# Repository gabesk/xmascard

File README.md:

# xmascard
Merry Christmas!

Of course, this is a little late for Christmas; by now it's probably closer in temperature in the southern hemisphere. Nevertheless, better late than never.

Welcome to the Electronic Christmas Tree Christmas Card. As you no doubt figured out already, to get started just flip the switch and enjoy the light show. (If it’s not working, try moving the battery around a little; the bottom doesn’t always make a solid connection to the board.)

Additionally, this board is intended to be at least somewhat more than just an amusement; you can do things with it, and the entire schematic and program are open source on GitHub for you to see.

It’s powered by a Xilinx FPGA, and you can add new patterns by connecting a serial cable to three pins near the FPGA with the included USB-serial adapter.

## History
The idea of this board started when Emily was playing with an Arduino one Christmas while I was looking at one of the myriad cards we’d received from friends, and I was remarking that it would be neat to take one of our Arduinos, some leftover LEDs, and see what sort of Christmas tree shaped thing we could make as a geeky card of some sort. The Arduino had 13 I/O ports, so a few minutes of brainstorming later, she came up with a 12 LED Christmas tree that looked neat.

As is my style, I couldn't leave well enough alone and keep things simple, however. First, as an undergrad I'd designed my own printed circuit boards (PCBs) and thought this would be a good excuse to re-learn how to do it. So, instead of a few LEDs wired up to an Arduino, it turned into a custom board. Additionally, I did my master’s thesis on FPGAs and I wanted an excuse both to work with them again, as well as the opportunity to introduce people to them. Given that, I thought it would be fun to use an FPGA in this Christmas card because it's typically seen as this exotic thing that is expensive and only used in specialize projects, and I wanted to change that perception.

This idea was actually conceived in January of 2015; I had no idea it would be so hard or take so long, but here we are, a year and a half later and I've finally stopped procrastinating enough to get something out the door.

## Interacting with the board
Initially, when this was just going to be a simple one-month project, the goal was just to display a pretty light pattern when you flipped the switch.

However, eventually the former-TA inside got the better of me and I decided I wanted to make it a little more interesting than just something you looked at once and put in a drawer. Toward that end, you'll also find some additional gizmos that you can use, with some assembly required, to interact with the board with your computer.

Included with the board are a USB-serial converter cable, a voltage regulator board, and some jumper wires to connect them together.

To get started, connect those pieces to the FPGA according to the following diagram:

If you're on a Windows or Linux computer, you're all set to run the programs.

If you're on a Mac, you'll need to download and install the driver for the USB-serial converter. Follow [the instructions](https://learn.adafruit.com/adafruits-raspberry-pi-lesson-5-using-a-console-cable/software-installation-mac) on AdaFruit's site this website for the SiLabs CP210X Drivers.

That done, double click the `light_control.py` file on your computer. It should open a window that looks similar to the following:

Click **Connect**, and follow the instructions. It will ask you to plug in the Christmas Tree board, and if all goes well, it will print that it was successfully connected in the bottom of the window.

Now that you're connected, click any of the lights on the tree. They should change on the board, too! :)

## Creating your own patterns
What else can you do? Well, you can make your own patterns, using the `convert_animation_file.py` and `upload_new_pattern.py` programs.

These programs accept text files containing animations patterns and downloads them to the board for display.

The animation files work like so:

Each step in the animation is specified on a line. Each line specifies the brightness of the LEDs, from the top left to the bottom right. Each LED is two digits from 0 to 7 for the red, then green brightness. The value 0 is off, while 7 is all the way bright. For readability, spaces can be added as desired and are ignored.

For example, to light the red LED on the top, then the entire row of green on the bottom, the line would look like the following:

```
70  00  00 00  00 00 00  07 07 07 07  00
```

Since that can still be hard to read, you can alternately put the LEDs on different lines and separate each step in the animation with a blank line.

This allows you to write the pattern out visually. For example, the above example could also be written as:

```
            70
            00
          00  00
        00  00  00
      07  07  07  07
            00
```

The animation runs at a fixed speed of # frames per second, and the board stores 256 animation steps for a total of # seconds of animation. If you don't use all 256 frames of animation, the program will just repeat the last frame until memory is full.

In order to make it a little easier to create animations, you can tell the program to fade between animation steps automatically.
For example, to create an animation which fades between all the LEDs on, off again, then back on, create a text file like so:

```
set_marker
       77
       77
     77  77
   77  77  77
 77  77  77  77
       77
       77
fade_to
       00
       00
     00  00
   00  00  00
 00  00  00  00
       00
fade_to
       77
       77
     77  77
   77  77  77
 77  77  77  77
       77
       77
repeat_forever
```

Suppose your text file is named animation.txt. First, convert it to an FPGA memory entry like so:
```
convert_animation_file.py animation.txt memory.txt
```
Next, program it to the FPGA like so:
```
upload_new_pattern.py COM3 memory.txt
```
You can find the correct value to use for COM3 by running the `light_control.py` and looking at the value in the box at the bottom of the program after clicking **Connect**.
If everything went well, you should see your animation running on the FPGA. If not, well, you can either treat this as an exercise in learning about Python, or email me and I'll help. :)

## Building the Project For Yourself
It's also possible to build the hardware design that runs on the FPGA for yourself, in order to experiment with making changes. To do so, follow these instructions. Note that while you don't need any additional hardware to build and simulate the hardware design, you will need either a flash memory programmer or a JTAG cable in order to actually try out your design on the actual board.

### Tools required for design synthesis:
- Xilinx ISE. Version 14.7 tested, but any reasonably recent version should work.
	As of mid-2017, for Windows, follow these steps to obtain it:
	- Navigate to xilinx.com
	- Scroll to bottom, click Downloads and Licensing.
	- Click ISE tab.
	- Choose either the multi-part or full download of ISE.
	- Create a new account.
	- Once software is installed and it asks for a license, choose a WebPack license.
	- **NOTE:** If running on Windows newer than Windows 7 (Windows 8.1 or Windows 10 at the time of this writing), follow [this application note](https://www.xilinx.com/support/answers/62380.html) to modify one of the DLLs included with the software to avoid a crash.

- Python. Python 2.7 or later is fine.

### Tools required for programming a new design:
- A way to write new images to a SPI flash chip. For this project, I used:
	- [FlashROM for Windows](http://ra.openbios.org/~idwer/flashrom/mingw/)
	- [BusPirate v3.6](http://dangerousprototypes.com/docs/Bus_Pirate)

- Alternately, a JTAG programmer. For this project, I used:
	- the [Digilent JTAG-HS3](http://store.digilentinc.com/jtag-hs3-programming-cable/) cable along with the Adept software (at the same link).

### Creating the built-in waterfall pattern
Before synthesis, open a command prompt and run the following two commands in the root of the directory where you cloned the project:
```
gen_top_down_waterfall_pattern.py built_in_pattern.txt
mif2coe.py built_in_pattern.txt > hdl\waterfall.coe
```

These commands generate the build-in waterfall image and format it in a way that the Xilinx tools accept into the on-FPGA BlockRAM memories.

### Synthesizing the design
- Launch the *Xilinx ISE Project Navigator*.
- Click *Open Project*, and choose `hdl\xilinx_project\xilinx_project.xise`.
- In the *Design* tab on the left of the screen, double-click on *Generate Programming File*. This will also run the *Synthesize* and *Implement Design* steps.
	- The tool will prompt about regenerating the `ram72bit` IP core. Click *Yes* to allow it to do so.
	- When complete, none of three steps should have a red X next to their name, and there should be a file `hdl\xilinx_project\lights.bit` containing the image to be programmed on the FPGA.

### Programming the design to the flash memory
- First, you'll need to connect the pins of the BusPirate to the pins of the flash memory chip.
	- Google for `MX25L4006E datasheet` to find the pinout of the memory chip.
	- Use a breadboard and some jumper wires to connect the two together.
- Open *Device Manager* and expand the *COM ports* section, then find the one associated with your BusPirate.
- Open `create_and_program_prom.cmd` in a text editor (right-cliking and choosing Edit will open it in Notepad, which is fine) and change the `COM#` to match what you found above.
- Open the *ISE Design Suite Command Prompt* as Administrator (by right-clicking on it) from the *Xilinx Design Tools* folder in the Start Menu.
- Navigate to the root directory of your clone.
- Run `create_and_program_prom.cmd`.

### Programming the design with the Digilent JTAG-HS3 JTAG programmer
- Power the FPGA by connecting it to the PC using the USB-serial cable.
- Connect the JTAG programmer to the connector on the FPGA.
- Run the Adept software. It should find the FPGA.
- Click *Browse*, choose `hdl\xilinx_project\lights.bit`, click *Program*.

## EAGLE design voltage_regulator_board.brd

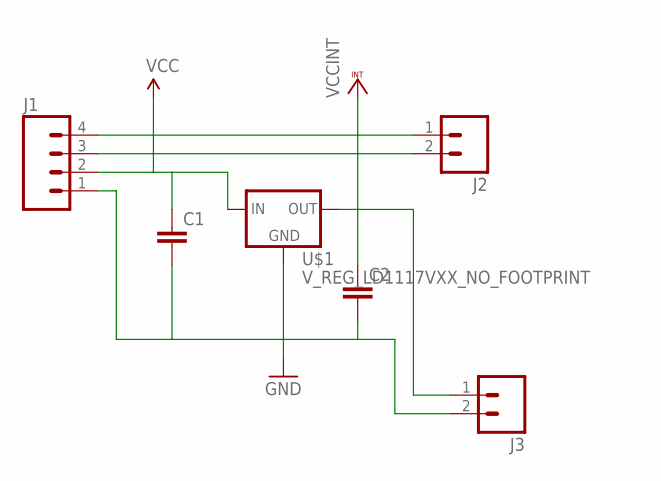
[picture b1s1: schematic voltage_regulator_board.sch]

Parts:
C1, C2: CAP0805; 0805
J1: M04LOCK; 1X04_LOCK
J2, J3: M02LOCK; 1X02_LOCK
U$1: V_REG_LD1117VXX_NO_FOOTPRINT; TO-220-NOFOOTPRINT

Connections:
GND: C1.2, C2.2, J1.1, J3.2, U$1.GND
unnamed: J1.4, J2.1
unnamed: J1.3, J2.2
VCC: C1.1, J1.2, U$1.IN
VCCINT: C2.1, J3.1, U$1.OUT

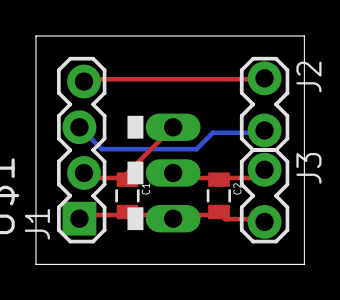
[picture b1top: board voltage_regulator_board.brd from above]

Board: 2 copper layers, 14.9 x 12.7 mm, 6 parts (0 on the bottom side), 5 nets.

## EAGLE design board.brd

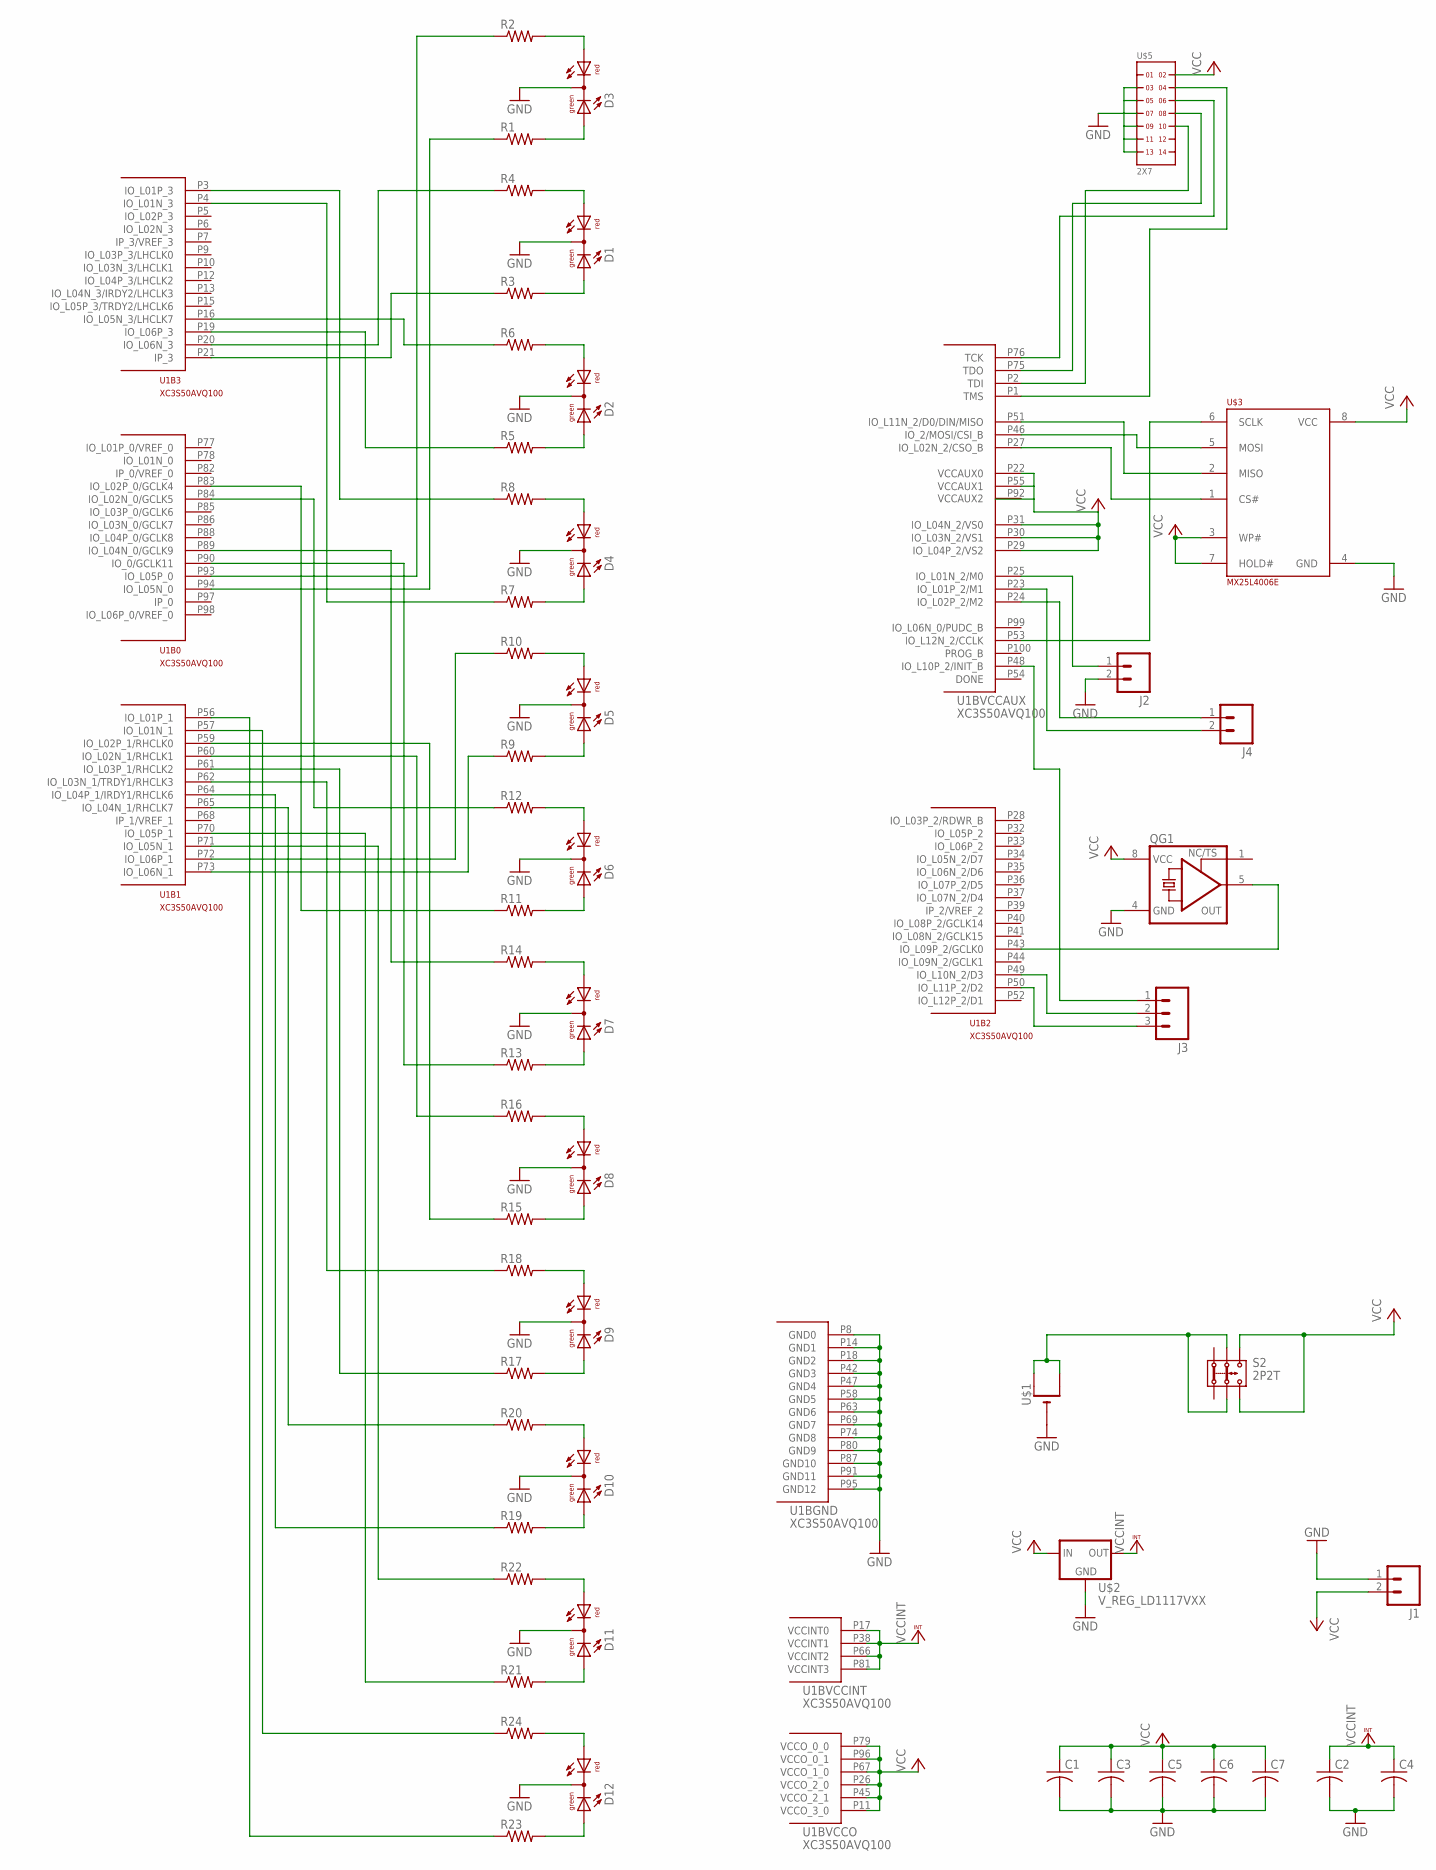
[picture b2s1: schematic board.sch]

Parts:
C1, C2, C3, C4, C5, C6, C7: C-USC0805; C0805
D1, D2, D3, D4, D5, D6, D7, D8, D9, D10, D11, D12: DUOLED5MM
J1, J2, J4: M02LOCK; 1X02_LOCK
J3: M03LOCK; 1X03_LOCK
QG1: XO-8; DIL08S
R1, R2, R3, R4, R5, R6, R7, R8, R9, R10, R11, R12, R13, R14, R15, R16, R17, R18, R19, R20, R21, R22, R23, R24: R-US_0204/7; 0204/7
S2: 2P2T
U1: XC3S50AVQ100; VQ100
U$1: CR2032THM; CR2032-THRU
U$2: V_REG_LD1117VXX; 78XXL
U$3: MX25L4006E; DIL08
U$5: 2X7

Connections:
CLK: QG1.5 (OUT), U1.P43 (IO_L09P_2/GCLK0)
GND: C1.2, C2.2, C3.2, C4.2, C5.2, C6.2, C7.2, D1.K (C), D2.K (C), D3.K (C), D4.K (C), D5.K (C), D6.K (C), D7.K (C), D8.K (C), D9.K (C), D10.K (C), D11.K (C), D12.K (C), J1.1, J2.2, QG1.4 (GND), U1.P8 (GND0), U1.P14 (GND1), U1.P18 (GND2), U1.P42 (GND3), U1.P47 (GND4), U1.P58 (GND5), U1.P63 (GND6), U1.P69 (GND7), U1.P74 (GND8), U1.P80 (GND9), U1.P87 (GND10), U1.P91 (GND11), U1.P95 (GND12), U$1.-, U$2.IN (GND), U$3.4 (GND), U$5.3, U$5.5, U$5.7, U$5.9, U$5.11, U$5.13
unnamed: U1.P1 (TMS), U$5.4
unnamed: S2.2.1, S2.2.2, U$1.+1 (+), U$1.+2 (+1)
unnamed: D1.AR, R4.2
unnamed: D3.AR, R2.2
unnamed: D1.AG, R3.2
unnamed: D2.AR, R6.2
unnamed: D2.AG, R5.2
unnamed: D4.AR, R8.2
unnamed: D3.AG, R1.2
unnamed: D4.AG, R7.2
unnamed: D5.AR, R10.2
unnamed: D5.AG, R9.2
unnamed: D6.AR, R12.2
unnamed: D6.AG, R11.2
unnamed: D7.AR, R14.2
unnamed: D7.AG, R13.2
unnamed: D8.AR, R16.2
unnamed: D8.AG, R15.2
unnamed: D9.AR, R18.2
unnamed: D9.AG, R17.2
unnamed: D10.AR, R20.2
unnamed: D10.AG, R19.2
unnamed: D11.AR, R22.2
unnamed: D11.AG, R21.2
unnamed: D12.AR, R24.2
unnamed: D12.AG, R23.2
unnamed: U1.P2 (TDI), U$5.10
unnamed: U1.P75 (TDO), U$5.8
unnamed: U1.P76 (TCK), U$5.6
unnamed: J3.3, U1.P50 (IO_L11P_2/D2)
unnamed: J3.2, U1.P49 (IO_L10N_2/D3)
unnamed: J3.1, U1.P48 (IO_L10P_2/INIT_B)
unnamed: U1.P51 (IO_L11N_2/D0/DIN/MISO), U$3.2 (MISO)
unnamed: U1.P46 (IO_2/MOSI/CSI_B), U$3.5 (MOSI)
unnamed: U1.P27 (IO_L02N_2/CSO_B), U$3.1 (CS#)
unnamed: U1.P53 (IO_L12N_2/CCLK), U$3.6 (SCLK)
unnamed: J4.1, U1.P24 (IO_L02P_2/M2)
unnamed: J4.2, U1.P23 (IO_L01P_2/M1)
unnamed: R3.1, U1.P21 (IP_3)
unnamed: R4.1, U1.P20 (IO_L06N_3)
unnamed: R5.1, U1.P19 (IO_L06P_3)
unnamed: R6.1, U1.P16 (IO_L05N_3/LHCLK7)
unnamed: R7.1, U1.P4 (IO_L01N_3)
unnamed: R8.1, U1.P3 (IO_L01P_3)
unnamed: R2.1, U1.P93 (IO_L05P_0)
unnamed: R1.1, U1.P94 (IO_L05N_0)
unnamed: R13.1, U1.P90 (IO_0/GCLK11)
unnamed: R14.1, U1.P89 (IO_L04N_0/GCLK9)
unnamed: R12.1, U1.P84 (IO_L02N_0/GCLK5)
unnamed: R11.1, U1.P83 (IO_L02P_0/GCLK4)
unnamed: R10.1, U1.P72 (IO_L06P_1)
unnamed: R9.1, U1.P73 (IO_L06N_1)
unnamed: R22.1, U1.P71 (IO_L05N_1)
unnamed: R21.1, U1.P70 (IO_L05P_1)
unnamed: R20.1, U1.P65 (IO_L04N_1/RHCLK7)
unnamed: R19.1, U1.P64 (IO_L04P_1/IRDY1/RHCLK6)
unnamed: R18.1, U1.P62 (IO_L03N_1/TRDY1/RHCLK3)
unnamed: R17.1, U1.P61 (IO_L03P_1/RHCLK2)
unnamed: R16.1, U1.P60 (IO_L02N_1/RHCLK1)
unnamed: R15.1, U1.P59 (IO_L02P_1/RHCLK0)
unnamed: R24.1, U1.P57 (IO_L01N_1)
unnamed: R23.1, U1.P56 (IO_L01P_1)
unnamed: J2.1, U1.P25 (IO_L01N_2/M0)
VCC: C1.1, C3.1, C5.1, C6.1, C7.1, J1.2, QG1.8 (VCC), S2.3.1, S2.3.2, U1.P11 (VCCO_3_0), U1.P22 (VCCAUX0), U1.P26 (VCCO_2_0), U1.P29 (IO_L04P_2/VS2), U1.P30 (IO_L03N_2/VS1), U1.P31 (IO_L04N_2/VS0), U1.P45 (VCCO_2_1), U1.P55 (VCCAUX1), U1.P67 (VCCO_1_0), U1.P79 (VCCO_0_0), U1.P96 (VCCO_0_1), U$2.OUT (IN), U$3.3 (WP#), U$3.7 (HOLD#), U$3.8 (VCC), U$5.2
VCCINT: C2.1, C4.1, U1.P17 (VCCINT0), U1.P38 (VCCINT1), U1.P66 (VCCINT2), U1.P81 (VCCINT3), U$2.GND (OUT)

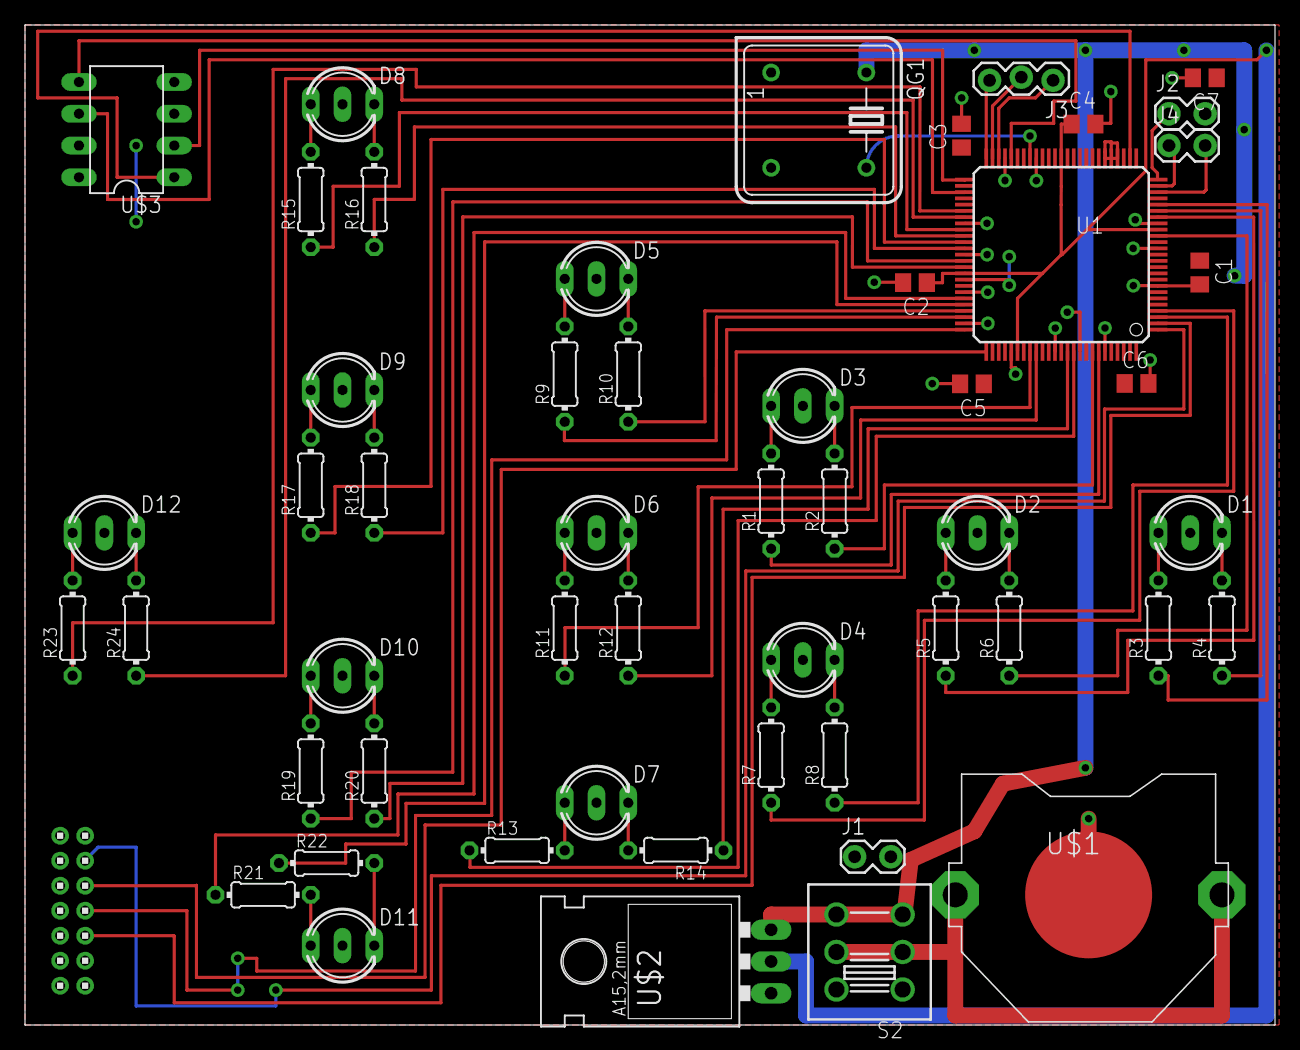
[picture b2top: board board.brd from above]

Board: 2 copper layers, 100.0 x 80.0 mm, 54 parts (0 on the bottom side), 67 nets.

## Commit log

2017-05-21 Initial commit HDL
2017-05-21 Initial commit (#1)
    * Initial commit
    * Initial commit HDL
2017-05-22 Initial writeup
2017-05-22 Initial writeup (#2)

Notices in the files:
parts and their libraries:
SparkFun-PowerIC: Licensing: Creative Commons ShareAlike 4.0 International - https://creativecommons.org/licenses/by-sa/4.0
